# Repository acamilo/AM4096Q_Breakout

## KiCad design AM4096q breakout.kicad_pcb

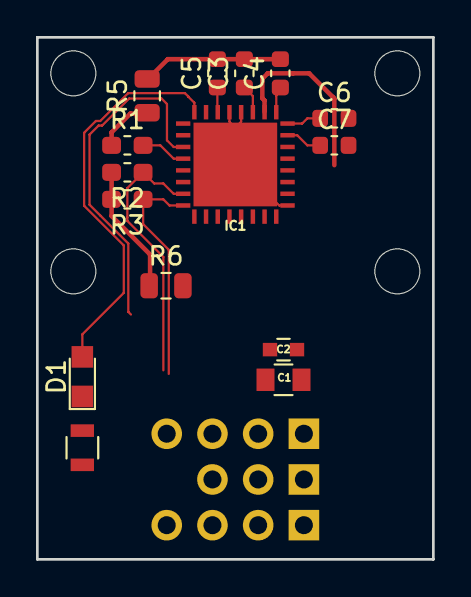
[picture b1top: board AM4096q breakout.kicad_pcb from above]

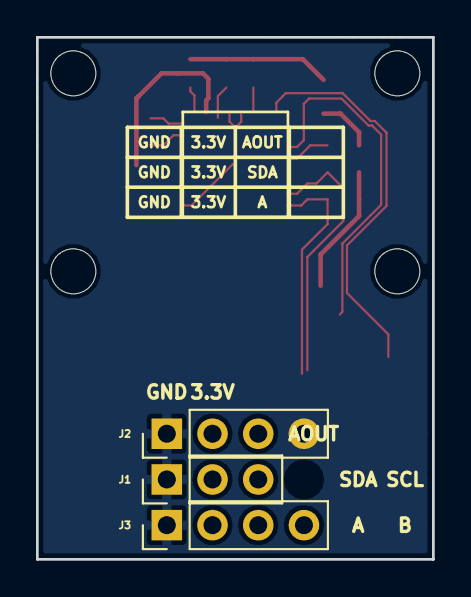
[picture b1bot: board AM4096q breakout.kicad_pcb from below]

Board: 2 copper layers, 22.0 x 29.0 mm, 18 parts (3 on the bottom side), 15 nets.

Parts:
C1: 10u 16v; C_0805
C2: 100nf; C_0603
C3, C4: 2.2u; C_0603_1608Metric
C5, C6, C7: 100n; C_0603_1608Metric
D1: LED; LED_0805
IC1: AM4096Q
J1: Conn_01x03; Pin_Header_Straight_1x03_Pitch2.54mm
J2, J3: Conn_01x04; Pin_Header_Straight_1x04_Pitch2.54mm
R1, R2, R3: 51K; R_0603_1608Metric_Pad1.05x0.95mm_HandSolder
R4: 330; R_0805
R5, R6: 0; R_0805_2012Metric

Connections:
A: IC1.16, J3.3
AOUT: IC1.3, J1.3
B: IC1.15, J3.4
GND: C1.2, C2.2, C3.2, C4.2, C5.2, C6.2, C7.2, IC1.17, IC1.28, IC1.29, IC1.33, J1.1, J2.1, J3.1, R1.1, R4.1, R5.1, R5.2
unnamed: C3.1, IC1.27
unnamed: C4.1, IC1.25
unnamed: C5.1, IC1.30
unnamed: C6.1, IC1.24
unnamed: C7.1, IC1.23
unnamed: D1.1, R4.2
unnamed: D1.2, IC1.32
unnamed: IC1.4, R1.2
SCL: IC1.8, J2.4, R3.1
SDA: IC1.7, J2.3, R2.1
VCC: C1.1, C2.1, IC1.26, J1.2, J2.2, J3.2, R2.2, R3.2, R6.1, R6.2

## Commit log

2018-06-13 Rev 1
2018-06-15 rev 1.1
2018-08-01 Updated Footprint
    Mirrored it and doubled lengths of pads
2018-08-01 Updated PCB
    Updated footorint. Re-routed parts of board.
2018-08-01 Remapped Symbols
2018-08-01 Added magnet presence LED
2018-10-04 updated schematic symbol
2018-10-04 Updated PCB with new required components and redid layout for single layer
